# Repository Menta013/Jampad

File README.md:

# Jampad

Jampad is a compact 3×3 mechanical macropad built around a through-hole
Seeed Studio XIAO RP2040. It includes an EC11 rotary encoder, a 0.91-inch
128×32 OLED, and a single SK6812 MINI-E status LED in a two-piece 3D-printed
enclosure.

## Project images

### Overall assembly and case

### Bottom case

### Top plate

### Schematic

### PCB

## Default controls

| Undo | Copy | Paste |
|---|---|---|
| Previous track | Play/Pause | Next track |
| Escape | Windows screenshot | Delete |

The encoder controls system volume:

- Counter-clockwise: volume down
- Clockwise: volume up
- Press: unavailable because the encoder's `S1` and `S2` switch contacts are
  not connected in this PCB revision

## Hardware

- MCU: Seeed Studio XIAO RP2040
- Switches: 9× Cherry MX-compatible switches in a diode-protected 3×3 matrix
- Display: 0.91-inch SSD1306-compatible 128×32 I²C OLED
- Encoder: EC11-style quadrature rotary encoder
- Lighting: 1× SK6812 MINI-E addressable RGB LED
- PCB: two layers, approximately 76.2 × 99.54 mm
- Case: two-piece 3D-printed enclosure

## Firmware pin map

| Function | XIAO pin | RP2040 GPIO |
|---|---:|---:|
| Matrix row 0 | D0 | GP26 |
| Matrix row 1 | D1 | GP27 |
| Matrix row 2 | D2 | GP28 |
| Matrix column 0 | D3 | GP29 |
| OLED SDA | D4 | GP6 |
| OLED SCL | D5 | GP7 |
| Matrix column 1 | D6 | GP0 |
| Matrix column 2 | D7 | GP1 |
| Encoder A | D8 | GP2 |
| Encoder B | D9 | GP4 |
| SK6812 data | D10 | GP3 |

The matrix diode direction is `COL2ROW`.

## Bill of materials

| Quantity | Part | Notes |
|---:|---|---|
| 1 | Seeed Studio XIAO RP2040 | Through-hole mounted |
| 9 | MX-compatible mechanical switches | PCB-mount style |
| 9 | MX-compatible keycaps | 1U |
| 9 | 1N4148 through-hole diodes | Matrix diodes |
| 1 | EC11-style rotary encoder | Rotation is wired; push switch is not |
| 1 | Encoder knob | Sized for the selected shaft |
| 1 | 0.91-inch 128×32 I²C OLED | SSD1306-compatible, four pins |
| 1 | SK6812 MINI-E | Addressable RGB status LED |
| 1 | Custom two-layer PCB | Maximum 100 × 100 mm |
| 1 | 3D-printed top case | Production STEP included |
| 1 | 3D-printed bottom case | Production STEP included |
| 4 | M3×16 mm screws | Confirm final stack height before ordering |
| 4 | M3 heat-set inserts | Approximately 4 mm OD × 5 mm long |

## Repository structure

```text
Jampad_Submission/
├── CAD/          # Full assembly source/export goes here
├── PCB/          # KiCad source files
├── Firmware/     # QMK source
├── production/   # Manufacturing and flash files
└── assets/       # README screenshots
```

## Firmware build

Copy `Firmware/` to `qmk_firmware/keyboards/jampad/`, then run:

```sh
qmk compile -kb jampad -km default
```

The compiled firmware is included as `production/firmware.uf2`.

To flash it, hold the XIAO's **BOOT** button while connecting USB, then copy
`firmware.uf2` to the `RPI-RP2` drive.

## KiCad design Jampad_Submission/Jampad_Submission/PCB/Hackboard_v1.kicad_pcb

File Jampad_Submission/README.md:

# Jampad

Jampad is a compact 3×3 mechanical macropad built around a through-hole
Seeed Studio XIAO RP2040. It includes an EC11 rotary encoder, a 0.91-inch
128×32 OLED, and a single SK6812 MINI-E status LED in a two-piece 3D-printed
enclosure.

> **Fabrication status:** the nine switch-to-diode connections have been
> repaired. KiCad reports zero unconnected pads and no copper-clearance
> errors. Final Gerbers and drill files are included in
> `production/gerbers.zip`. Review the remaining non-electrical DRC warnings
> in `production/drc_report.txt` before ordering.

## Project images

### Overall assembly and case

### Schematic

### PCB

## Default controls

| Undo | Copy | Paste |
|---|---|---|
| Previous track | Play/Pause | Next track |
| Escape | Windows screenshot | Delete |

The encoder controls system volume:

- Counter-clockwise: volume down
- Clockwise: volume up
- Press: unavailable because the encoder's `S1` and `S2` switch contacts are
  not connected in this PCB revision

## Hardware

- MCU: Seeed Studio XIAO RP2040
- Switches: 9× Cherry MX-compatible switches in a diode-protected 3×3 matrix
- Display: 0.91-inch SSD1306-compatible 128×32 I²C OLED
- Encoder: EC11-style quadrature rotary encoder
- Lighting: 1× SK6812 MINI-E addressable RGB LED
- PCB: two layers, approximately 76.2 × 99.54 mm
- Case: two-piece 3D-printed enclosure

## Firmware pin map

| Function | XIAO pin | RP2040 GPIO |
|---|---:|---:|
| Matrix row 0 | D0 | GP26 |
| Matrix row 1 | D1 | GP27 |
| Matrix row 2 | D2 | GP28 |
| Matrix column 0 | D3 | GP29 |
| OLED SDA | D4 | GP6 |
| OLED SCL | D5 | GP7 |
| Matrix column 1 | D6 | GP0 |
| Matrix column 2 | D7 | GP1 |
| Encoder A | D8 | GP2 |
| Encoder B | D9 | GP4 |
| SK6812 data | D10 | GP3 |

The matrix diode direction is `COL2ROW`.

## Bill of materials

| Quantity | Part | Notes |
|---:|---|---|
| 1 | Seeed Studio XIAO RP2040 | Through-hole mounted |
| 9 | MX-compatible mechanical switches | PCB-mount style |
| 9 | MX-compatible keycaps | 1U |
| 9 | 1N4148 through-hole diodes | Matrix diodes |
| 1 | EC11-style rotary encoder | Rotation is wired; push switch is not |
| 1 | Encoder knob | Sized for the selected shaft |
| 1 | 0.91-inch 128×32 I²C OLED | SSD1306-compatible, four pins |
| 1 | SK6812 MINI-E | Addressable RGB status LED |
| 1 | Custom two-layer PCB | Maximum 100 × 100 mm |
| 1 | 3D-printed top case | Production STEP included |
| 1 | 3D-printed bottom case | Production STEP included |
| 4 | M3×16 mm screws | Confirm final stack height before ordering |
| 4 | M3 heat-set inserts | Approximately 4 mm OD × 5 mm long |

## Repository structure

```text
Jampad_Submission/
├── CAD/          # Full assembly source/export goes here
├── PCB/          # KiCad source files
├── Firmware/     # QMK source
├── production/   # Manufacturing and flash files
└── assets/       # README screenshots
```

## Firmware build

Copy `Firmware/` to `qmk_firmware/keyboards/jampad/`, then run:

```sh
qmk compile -kb jampad -km default
```

The compiled firmware is included as `production/firmware.uf2`.

To flash it, hold the XIAO's **BOOT** button while connecting USB, then copy
`firmware.uf2` to the `RPI-RP2` drive.

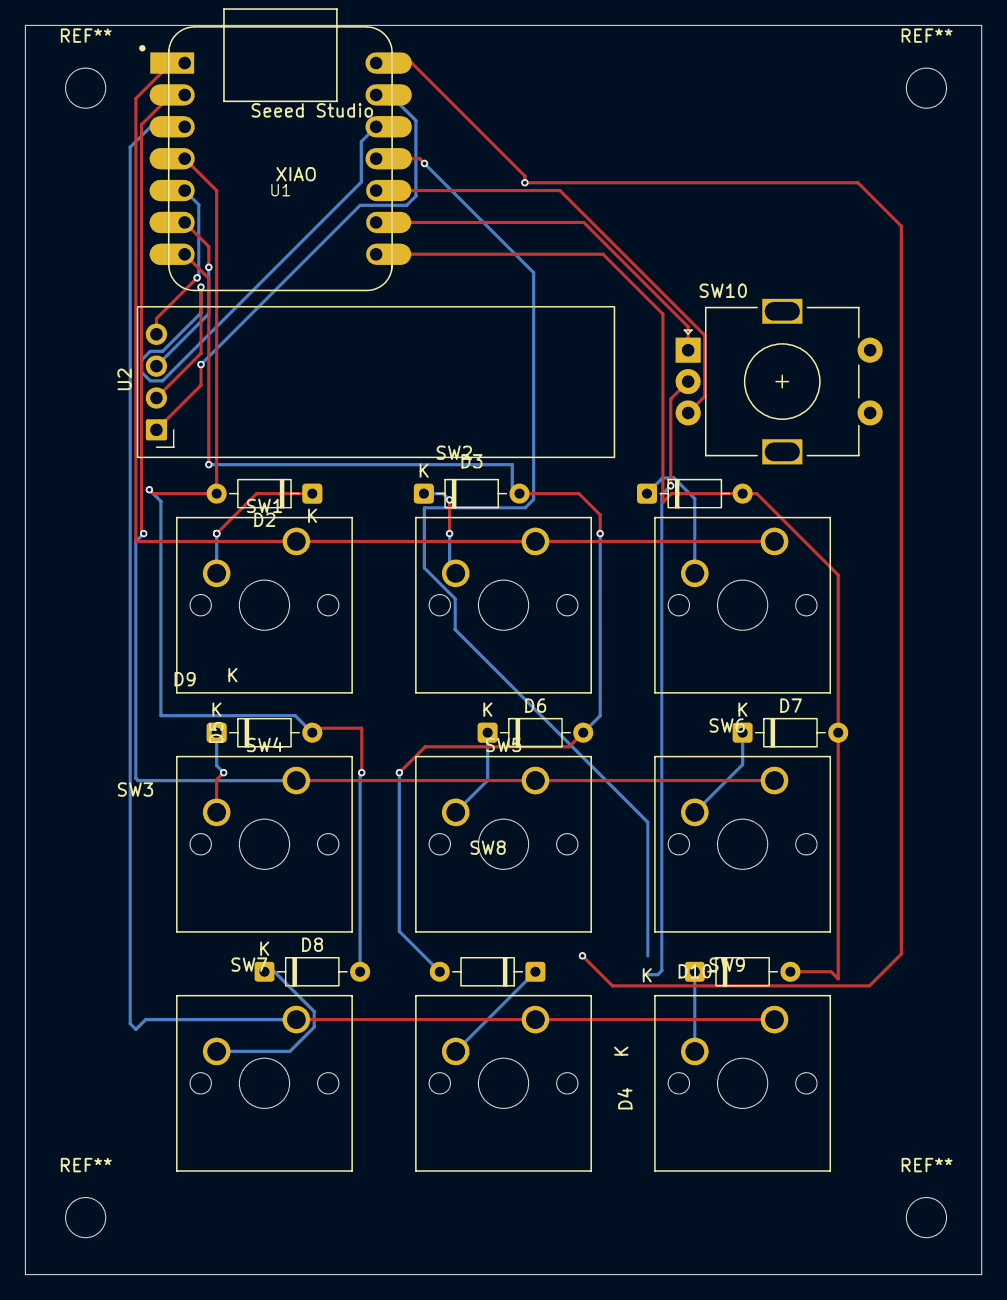
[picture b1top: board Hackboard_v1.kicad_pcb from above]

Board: 2 copper layers, 76.2 x 99.5 mm, 22 parts (0 on the bottom side), 24 nets.

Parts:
D1: SK6812MINI-E; SK6812MINI-E_fixed
D2, D3, D4, D5, D6, D7, D8, D9, D10: 1N4148; D_DO-35_SOD27_P7.62mm_Horizontal
SW1, SW2, SW3, SW4, SW5, SW6, SW7, SW8, SW9: SW_Push; SW_Cherry_MX_1.00u_PCB
SW10: RotaryEncoder_Switch; RotaryEncoder_Alps_EC11E-Switch_Vertical_H20mm
U1: MOUDLE-SEEEDUINO-XIAO; XIAO-Generic-Hybrid-14P-2.54-21X17.8MM
U2: ER_OLEDM0.91_1x-I2C

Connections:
/C0: D2.2 (A), D5.2 (A), D8.2 (A), U1.4 (PA11_A3_D3)
/C1: D3.2 (A), D6.2 (A), D9.2 (A), U1.7 (PB08_A6_D6_TX)
/C2: D4.2 (A), D7.2 (A), D10.2 (A), U1.8 (PB09_A7_D7_RX)
/ENC_A: SW10.A, U1.9 (PA7_A8_D8_SCK)
/ENC_B: SW10.B, U1.10 (PA5_A9_D9_MISO)
/R0: SW1.1, SW2.1, SW3.1, U1.1 (PA02_A0_D0)
/R1: SW4.1, SW5.1, SW6.1, U1.2 (PA4_A1_D1)
/R2: SW7.1, SW8.1, SW9.1, U1.3 (PA10_A2_D2)
GND: D1.3 (VSS), SW10.C
unnamed: D1.4 (DIN), U1.11 (PA6_A10_D10_MOSI)
unnamed: D1.1 (VDD), U1.14 (5V)
unnamed: D2.1 (K), SW1.2
unnamed: D3.1 (K), SW2.2
unnamed: D4.1 (K), SW3.2
unnamed: D5.1 (K), SW4.2
unnamed: D6.1 (K), SW5.2
unnamed: D7.1 (K), SW6.2
unnamed: D8.1 (K), SW7.2
unnamed: D9.1 (K), SW8.2
unnamed: D10.1 (K), SW9.2
unnamed: U1.12 (3V3), U2.2 (VCC)
unnamed: U1.13 (GND), U2.1 (GND)
unnamed: U1.5 (PA8_A4_D4_SDA), U2.4 (SDA)
unnamed: U1.6 (PA9_A5_D5_SCL), U2.3 (SCL)
